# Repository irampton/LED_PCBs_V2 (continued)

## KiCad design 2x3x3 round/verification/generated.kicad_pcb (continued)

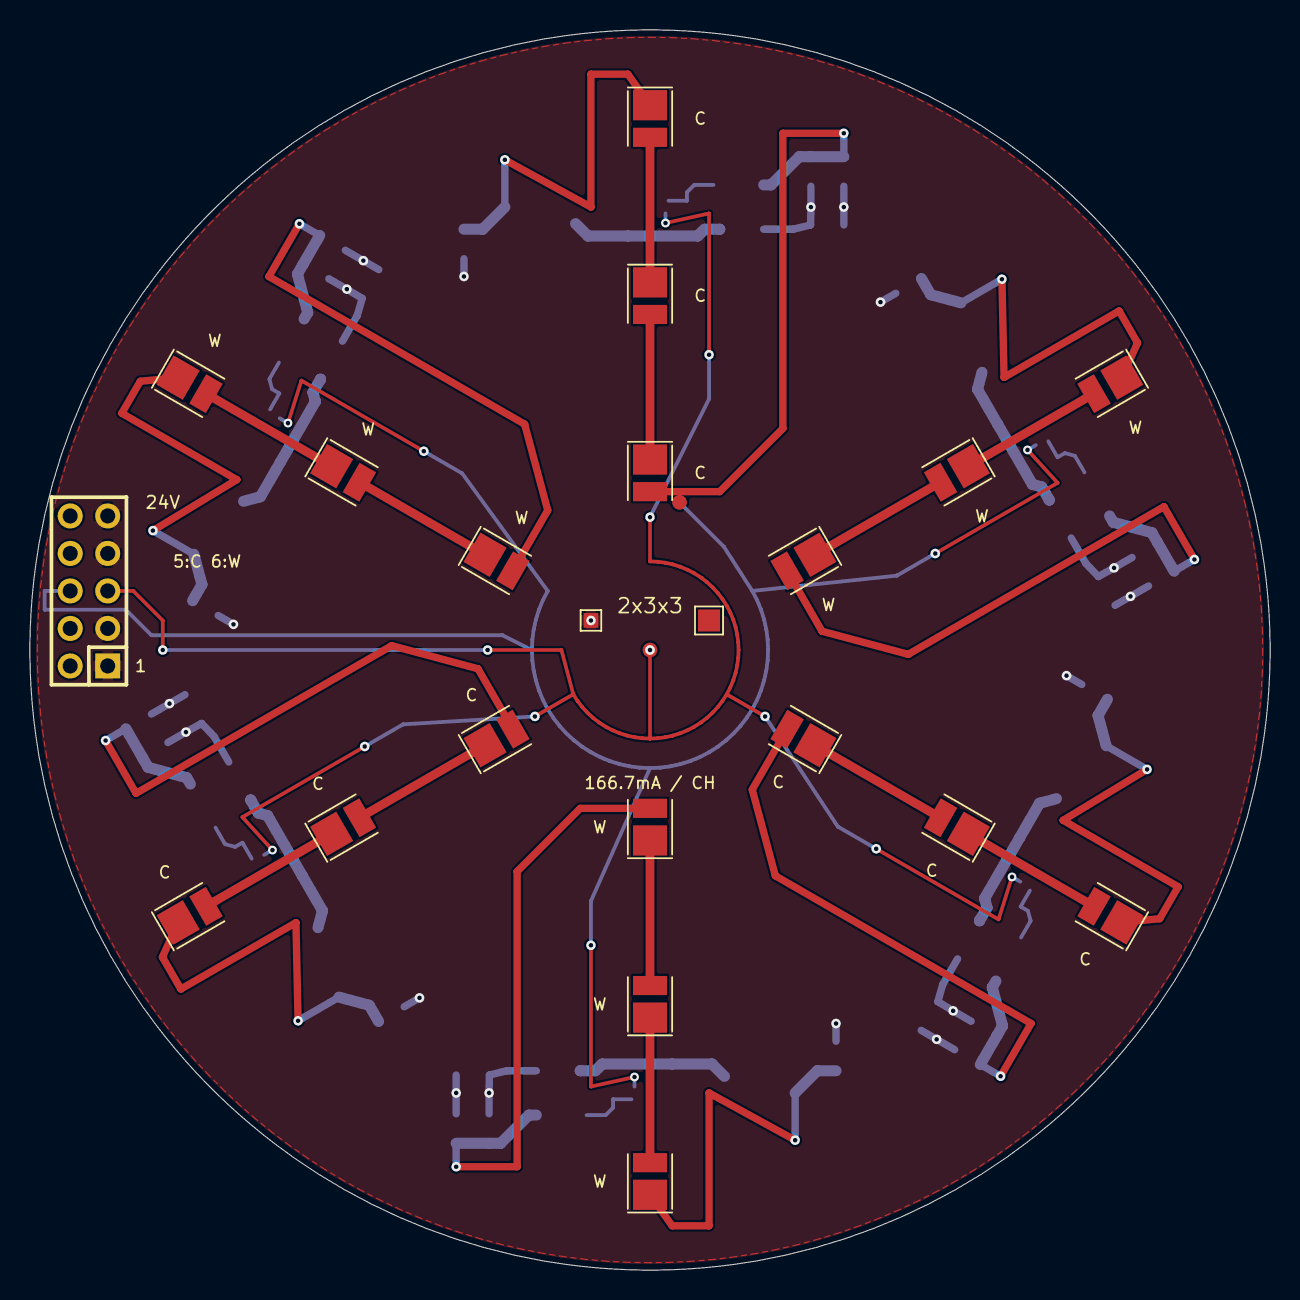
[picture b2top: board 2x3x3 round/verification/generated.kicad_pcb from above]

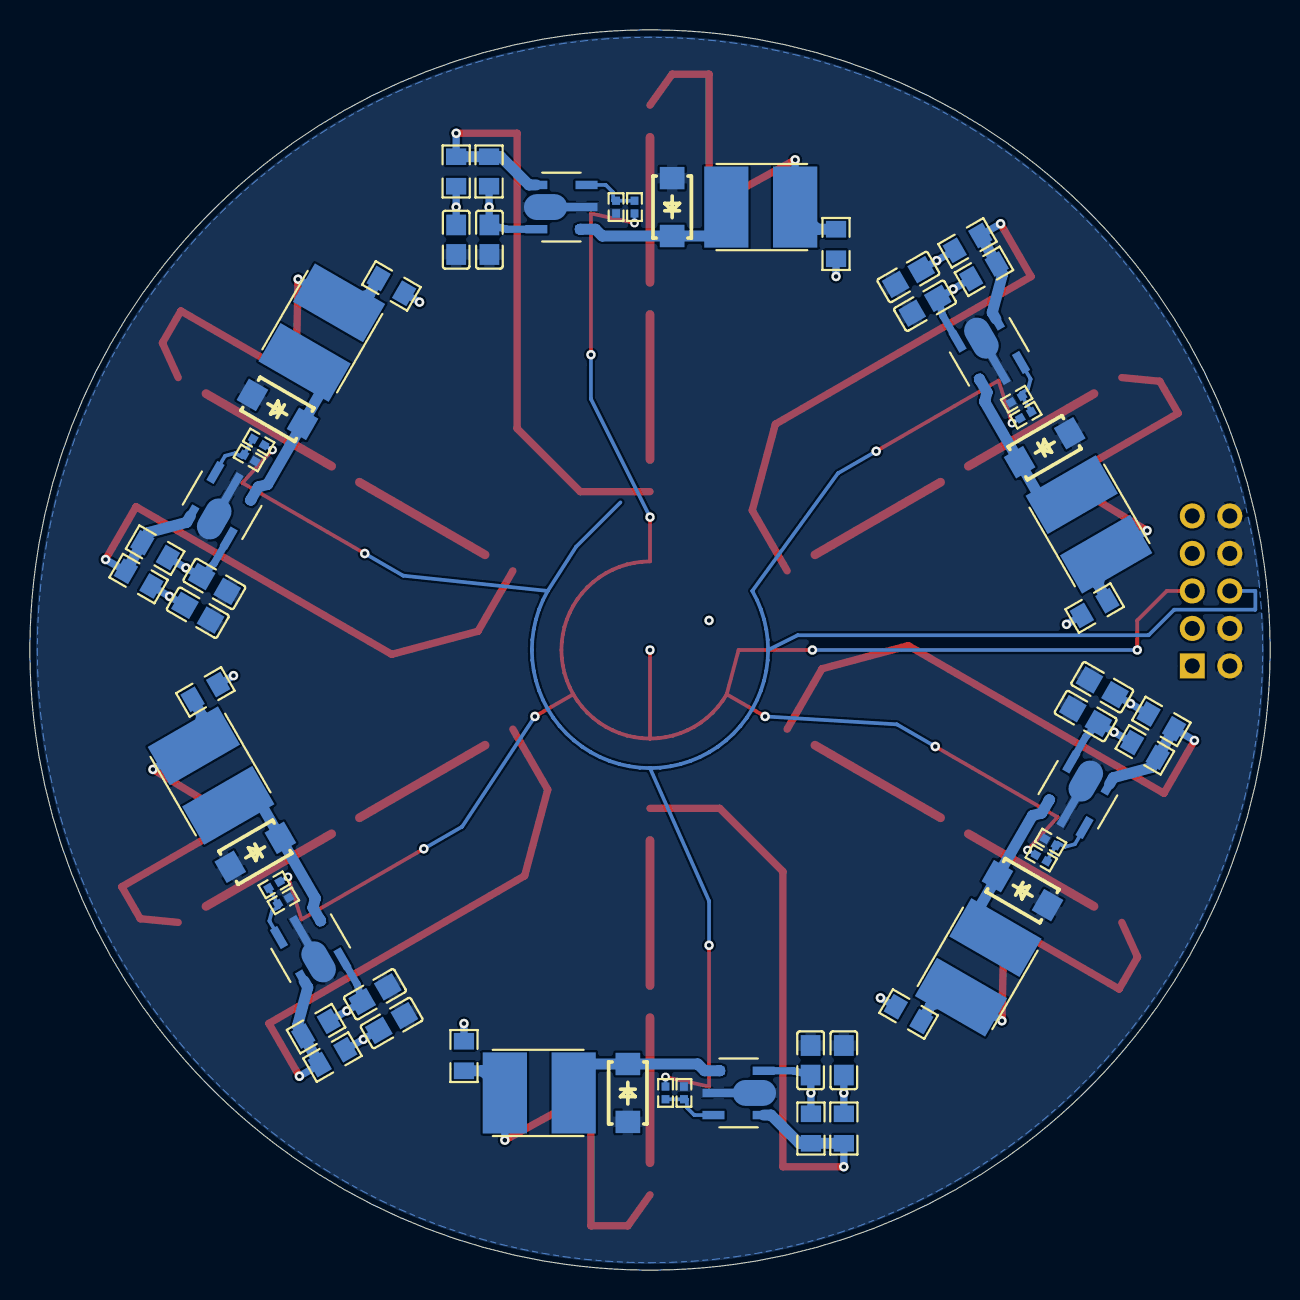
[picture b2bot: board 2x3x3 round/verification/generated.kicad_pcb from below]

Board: 2 copper layers, 84.0 x 84.0 mm, 83 parts (60 on the bottom side), 40 nets.

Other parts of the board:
C11, C12: 2.2uF; CL21A225KBQNNNE
D6: SS14
L6: 0.000068uH; CY54_68UH
R11, R12: 1.2; P_0805W8F120KT5E
R18: 100k; P_0402WGF1003TCE
R24: 10k; P_0805W8F1002T5E
R30: 2.2k; P_0402WGF2201TCE
U6: PT4115

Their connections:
GND: C11.2, C12.2, D6.2 (A), R18.2, U6.2; also elsewhere on the board
V+: C11.1, C12.1, R11.1, R12.1, R24.1, U6.5; also elsewhere on the board
pwm_warm: R30.1; also elsewhere on the board
warm_c_channel_LED_RETURN: L6.2, R24.2; also elsewhere on the board
warm_c_channel_LED_TOP: R11.2, R12.2, U6.4; also elsewhere on the board
warm_c_channel_driver_SW: D6.1 (K), L6.1, U6.1
warm_c_channel_pwm_2_2_1: R18.1, R30.2, U6.3

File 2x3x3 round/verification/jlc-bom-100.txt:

JLC BOM estimate for 100 boards

Basic
Designators                 Comment             Footprint         MPN              LCSC #   JLC Stock  Per Board
--------------------------  ------------------  ----------------  ---------------  -------  ---------  ---------
C1, C2, C3, C4, C5, C6,...  2.2uF ±10% 50V X5R  0805              CL21A225KBQNNNE  C377773     965001    $0.3108
D1, D2, D3, D4, D5, D6                          SMA_L4.2-W2.6...  SS14             C2480      1626545    $0.0912
R13, R14, R15, R16, R17...  100kΩ ±1% 62.5mW    0402              0402WGF1003TCE   C25741     8604931    $0.0072
R19, R20, R21, R22, R23...  10kΩ ±1% 125mW      0805              0805W8F1002T5E   C17414    49430616    $0.0204
R25, R26, R27, R28, R29...  2.2kΩ ±1% 62.5mW    0402              0402WGF2201TCE   C25879     3323646    $0.0066

Extended
Designators                 Comment          Footprint         MPN                         LCSC #     JLC Stock  Per Board
--------------------------  ---------------  ----------------  --------------------------  ---------  ---------  ---------
H1                                           HDR-TH_10P-P2...  PZ2.54-2X5P-H25             C42431818      24206    $0.0423
L1, L2, L3, L4, L5, L6      68uH ±10% 600mA  SMD,5.8x5.2mm     CY54-68UH                   C2929435       12384    $0.2376
LED1, LED2, LED3, LED4,...                   LED-SMD_L3.3-...  HL-AS-2835D68W-2C-S1-08...  C49435727       1153    $0.1800
LED10, LED11, LED12, LE...                   LED-SMD_L3.5-...  HL-AS-2835D68W-2C-S1-08...  C49435731      12953    $0.1755
R1, R2, R3, R4, R5, R6,...  1.2Ω ±1% 125mW   0805              0805W8F120KT5E              C17381         26335    $0.0480
U1, U2, U3, U4, U5, U6                       SOT-89-5_L4.5...  PT4115                      C347356        96127    $0.4506

Cost estimate only. These figures ignore board size, layer count, and SMD vs manual assembly.

Economic totals
2 boards   $32.25
5 boards   $39.37
15 boards  $59.52
30 boards  $82.49

Standard totals
5 boards     $61.05
30 boards    $104.17
100 boards   $217.72
1000 boards  $1865.48

Additional fees may apply: $3.50 hand-soldering, $59.23 large-sized boards, plus x-ray inspection and panel fees.
Double-sided boards require standard assembly, can add $25 setup, and add $7.86 stencil cost.

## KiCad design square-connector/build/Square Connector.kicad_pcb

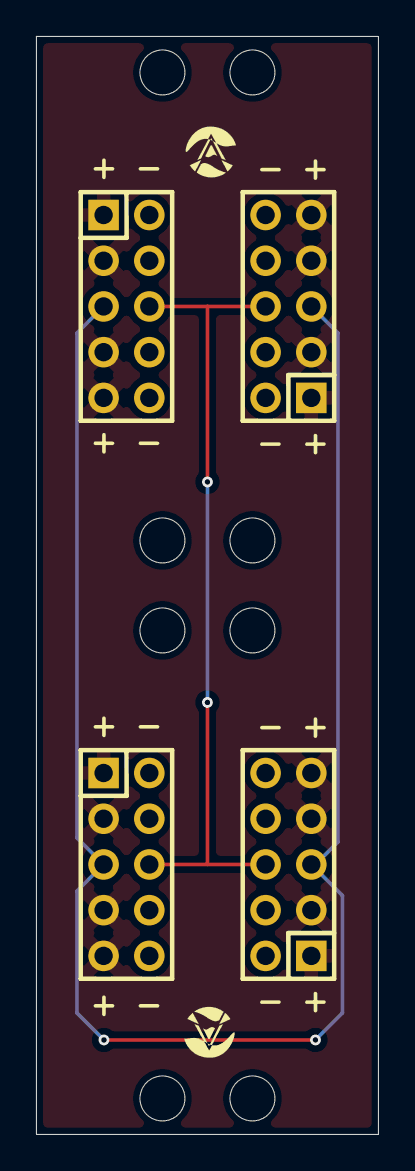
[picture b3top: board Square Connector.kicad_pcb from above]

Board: 2 copper layers, 19.0 x 61.0 mm, 4 parts (0 on the bottom side), 4 nets.

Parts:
H3, H4, H5, H6: PZ2.54-2X5P-H25; PZ2_54_2X5P_H25

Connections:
/GND: H3.2, H3.4, H3.8, H3.10, H4.2, H4.4, H4.8, H4.10, H5.2, H5.4, H5.8, H5.10, H6.2, H6.4, H6.8, H6.10
/V+: H3.1, H3.3, H3.7, H3.9, H4.1, H4.3, H4.7, H4.9, H5.1, H5.3, H5.7, H5.9, H6.1, H6.3, H6.7, H6.9
/pwm_cool: H3.5, H4.5, H5.5, H6.5
/pwm_warm: H3.6, H4.6, H5.6, H6.6
